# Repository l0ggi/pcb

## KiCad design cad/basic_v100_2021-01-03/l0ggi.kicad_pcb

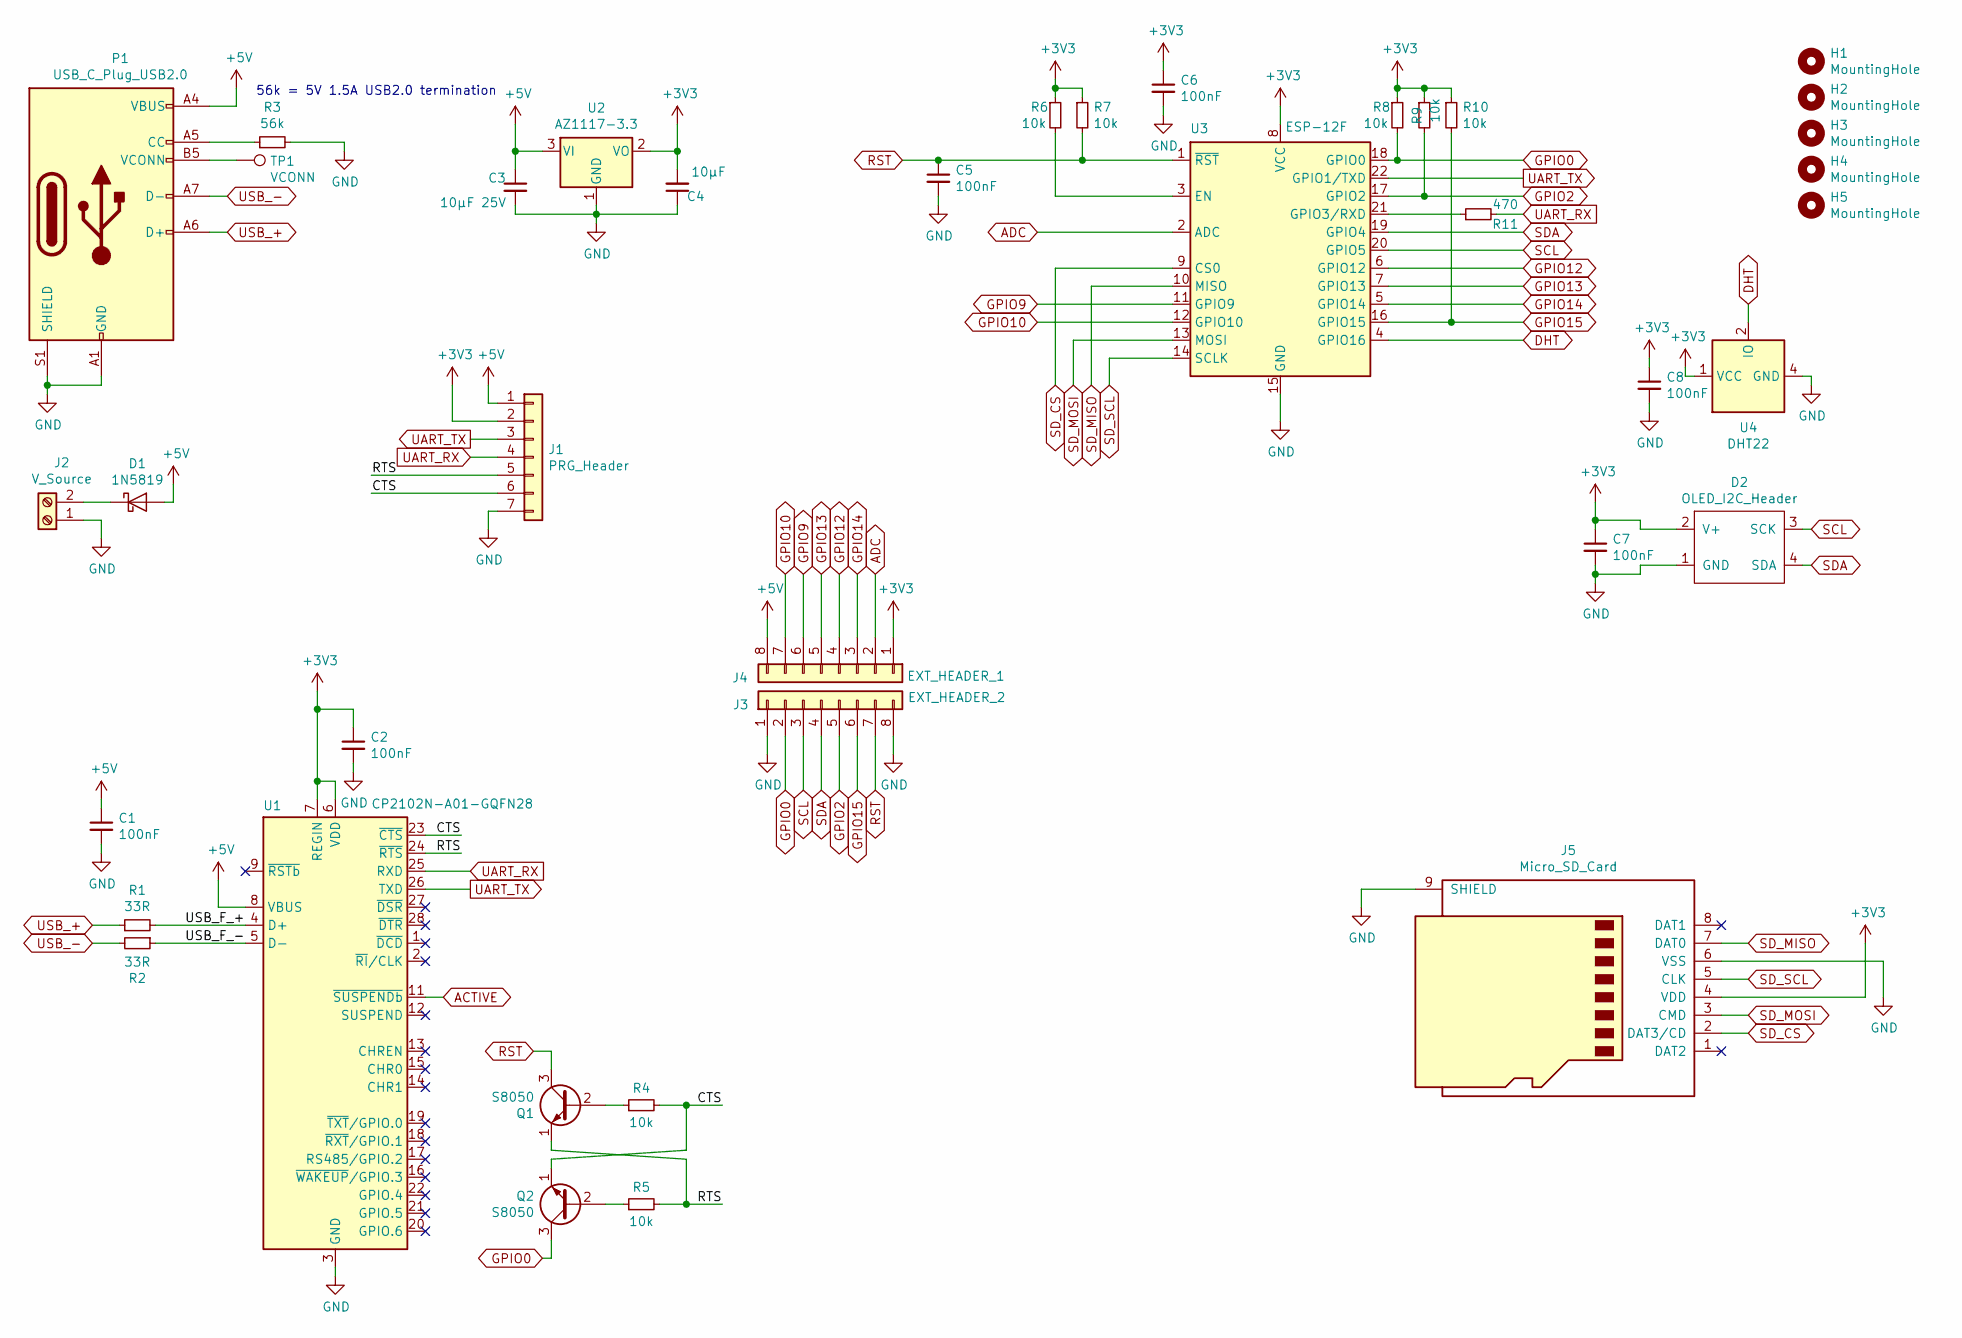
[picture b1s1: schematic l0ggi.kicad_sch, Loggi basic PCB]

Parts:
C1, C2, C5, C6, C7, C8: 100nF; C_0603_1608Metric; LCSC C14663
C3: 10µF 25V; C_0603_1608Metric; LCSC C96446
C4: 10µF; C_0603_1608Metric; LCSC C19702
D1: 1N5819; D_SOD-323; LCSC C191023
D2: OLED_I2C_Header; PinHeader_1x04_P2.54mm_Vertical
H1, H2, H3, H4, H5: MountingHole; MountingHole_2.7mm_M2.5
J1: PRG_Header; PinHeader_1x07_P2.54mm_Vertical
J2: V_Source; TerminalBlock_bornier-2_P5.08mm
J3: EXT_HEADER_2; PinHeader_1x08_P2.54mm_Vertical
J4: EXT_HEADER_1; PinHeader_1x08_P2.54mm_Vertical
J5: Micro_SD_Card; microSD_HC_Wuerth_693072010801
P1: USB_C_Plug_USB2.0; USB_C_Receptacle_GCT_USB4085
Q1, Q2: S8050; SOT-23; LCSC C2146
R1, R2: 33R; R_0603_1608Metric; LCSC C23140
R3: 56k; R_0603_1608Metric; LCSC C23206
R4, R5, R6, R7, R8, R9, R10: 10k; R_0603_1608Metric; LCSC C25804
R11: 470; R_0603_1608Metric; LCSC C23179
TP1: VCONN; TestPoint_Pad_D1.0mm
U1: CP2102N-A01-GQFN28; QFN-28-1EP_5x5mm_P0.5mm_EP3.35x3.35mm; LCSC C6568
U2: AZ1117-3.3; SOT-223-3_TabPin2; LCSC C6186
U3: ESP-12F; ESP-12E; LCSC C82891
U4: DHT22; Aosong_DHT11_5.5x12.0_P2.54mm

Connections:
+3V3: C2.1, C4.2, C6.1, C7.1, C8.1, D2.2 (V+), J1.2, J4.1, J5.4 (VDD), R6.1, R7.1, R8.1, R9.1, R10.1, U1.6 (VDD), U1.7 (REGIN), U2.2 (VO), U3.8 (VCC), U4.1 (VCC)
+5V: C1.1, C3.1, D1.2 (A), J1.1, J4.8, P1.A4 (VBUS), P1.A9 (VBUS), P1.B4 (VBUS), P1.B9 (VBUS), U1.8 (VBUS), U2.3 (VI)
/CTS: J1.6, Q2.1 (E), R4.2, U1.23 (~CTS)
/RTS: J1.5, Q1.1 (E), R5.2, U1.24 (~RTS)
/USB_F_+: R1.2, U1.4 (D+)
/USB_F_-: R2.1, U1.5 (D-)
ADC: J4.2, U3.2 (ADC)
DHT: U3.4 (GPIO16), U4.2 (IO)
GND: C1.2, C2.2, C3.2, C4.1, C5.2, C6.2, C7.2, C8.2, D2.1 (GND), J1.7, J2.1, J3.1, J3.8, J5.6 (VSS), J5.9 (SHIELD), P1.A1 (GND), P1.A12 (GND), P1.B1 (GND), P1.B12 (GND), P1.S1 (SHIELD), R3.2, U1.3 (GND), U1.29 (GND), U2.1 (GND), U3.15 (GND), U4.4 (GND)
GPIO0: J3.2, Q2.3 (C), R8.2, U3.18 (GPIO0)
GPIO2: J3.5, R9.2, U3.17 (GPIO2)
GPIO9: J4.6, U3.11 (GPIO9)
GPIO10: J4.7, U3.12 (GPIO10)
GPIO12: J4.4, U3.6 (GPIO12)
GPIO13: J4.5, U3.7 (GPIO13)
GPIO14: J4.3, U3.5 (GPIO14)
GPIO15: J3.6, R10.2, U3.16 (GPIO15)
unnamed: D1.1 (K), J2.2
unnamed: P1.A5 (CC), R3.1
unnamed: P1.B5 (VCONN), TP1.1
unnamed: Q1.2 (B), R4.1
unnamed: Q2.2 (B), R5.1
unnamed: R6.2, U3.3 (EN)
unnamed: R11.1, U3.21 (GPIO3/RXD)
RST: C5.1, J3.7, Q1.3 (C), R7.2, U3.1 (~RST)
SCL: D2.3 (SCK), J3.3, U3.20 (GPIO5)
SDA: D2.4 (SDA), J3.4, U3.19 (GPIO4)
SD_CS: J5.2 (DAT3/CD), U3.9 (CS0)
SD_MISO: J5.7 (DAT0), U3.10 (MISO)
SD_MOSI: J5.3 (CMD), U3.13 (MOSI)
SD_SCL: J5.5 (CLK), U3.14 (SCLK)
UART_RX: J1.4, R11.2, U1.25 (RXD)
UART_TX: J1.3, U1.26 (TXD), U3.22 (GPIO1/TXD)
USB_+: P1.A6 (D+), R1.1
USB_-: P1.A7 (D-), R2.2

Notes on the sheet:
56k = 5V 1.5A USB2.0 termination

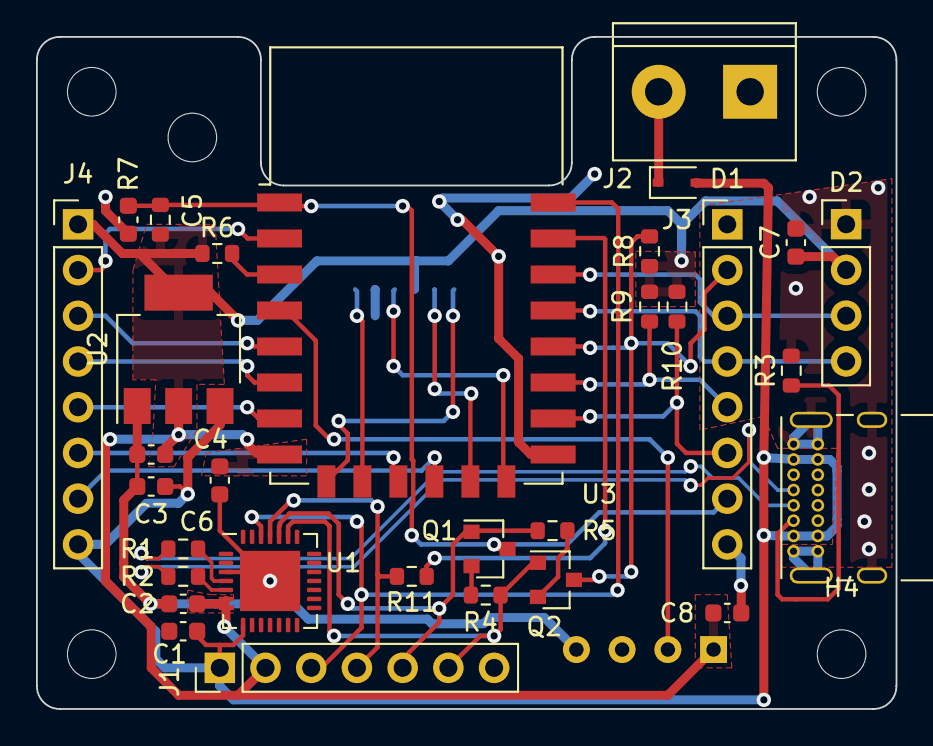
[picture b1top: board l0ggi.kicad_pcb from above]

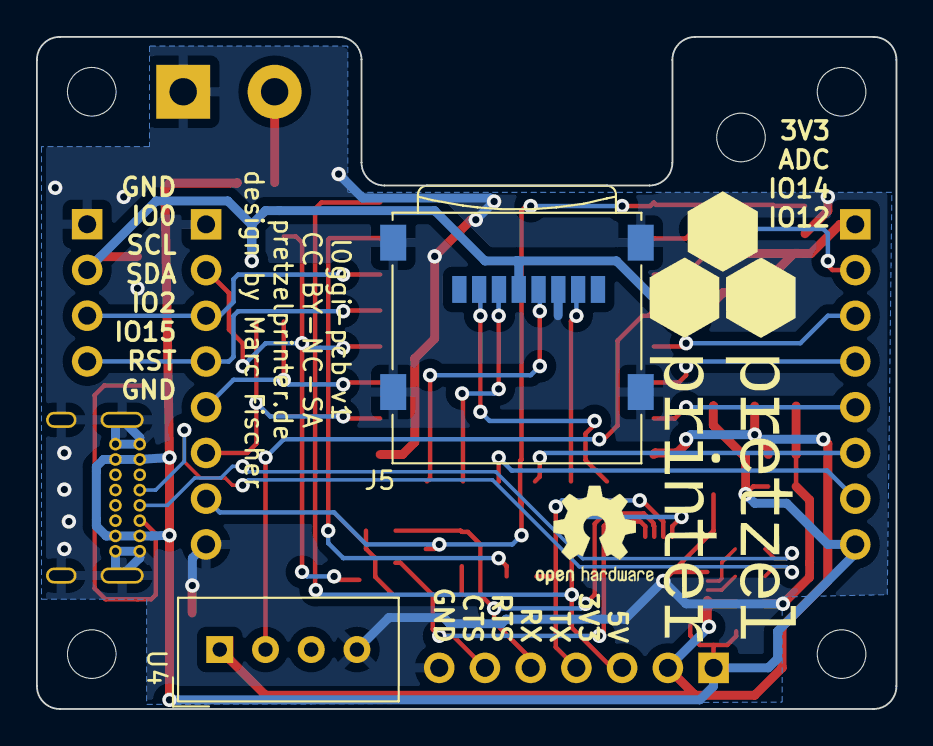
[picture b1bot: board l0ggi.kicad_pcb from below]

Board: 2 copper layers, 47.8 x 37.3 mm, 38 parts (2 on the bottom side), 34 nets.

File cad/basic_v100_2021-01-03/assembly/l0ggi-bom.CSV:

Designator;Quantity;Comment;Footprint;LCSCPart#
C1,C2,C5,C6,C7,C8;6;100nF;0603;C14663;
C3;1;10uF25V;0603;C96446;
C4;1;10uF;0603;C19702;
D1;1;1N5819;D-SOD-323;C191023;
Q1,Q2;2;S8050;SOT-23;C2146
R1,R2;2;33R;0603;C23140
R11;1;470;0603;C23179
R3;1;56k;0603;C23206
R4,R5,R6,R7,R8,R9,R10;7;10k;0603;C25804
U1;1;CP2102N-A01-GQFN28;QFN-28-1EP;C6568
U2;1;AZ1117-3.3;SOT-223-3;C6186
U3;1;ESP-12F;ESP-12E;C82891

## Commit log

2021-01-17 initial prototype pcb
2021-01-17 changed RX/TX, updated S8050 footprint, added temp sensor for pick and place

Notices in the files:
cad/basic_v100_2021-01-03/l0ggi.kicad_pcb:
CC BY-NC-SA
cad/basic_v100_2021-01-03/l0ggi.kicad_sch:
https://creativecommons.org/licenses/by-nc-sa/4.0/legalcode
Licensed by CC BY-NC-SA
